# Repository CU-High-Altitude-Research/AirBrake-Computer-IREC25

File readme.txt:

https://github.com/CDFER/JLCPCB-Kicad-Library
To add library: git submodule add https://github.com/CDFER/JLCPCB-Kicad-Library.git
To update: git submodule update --remote

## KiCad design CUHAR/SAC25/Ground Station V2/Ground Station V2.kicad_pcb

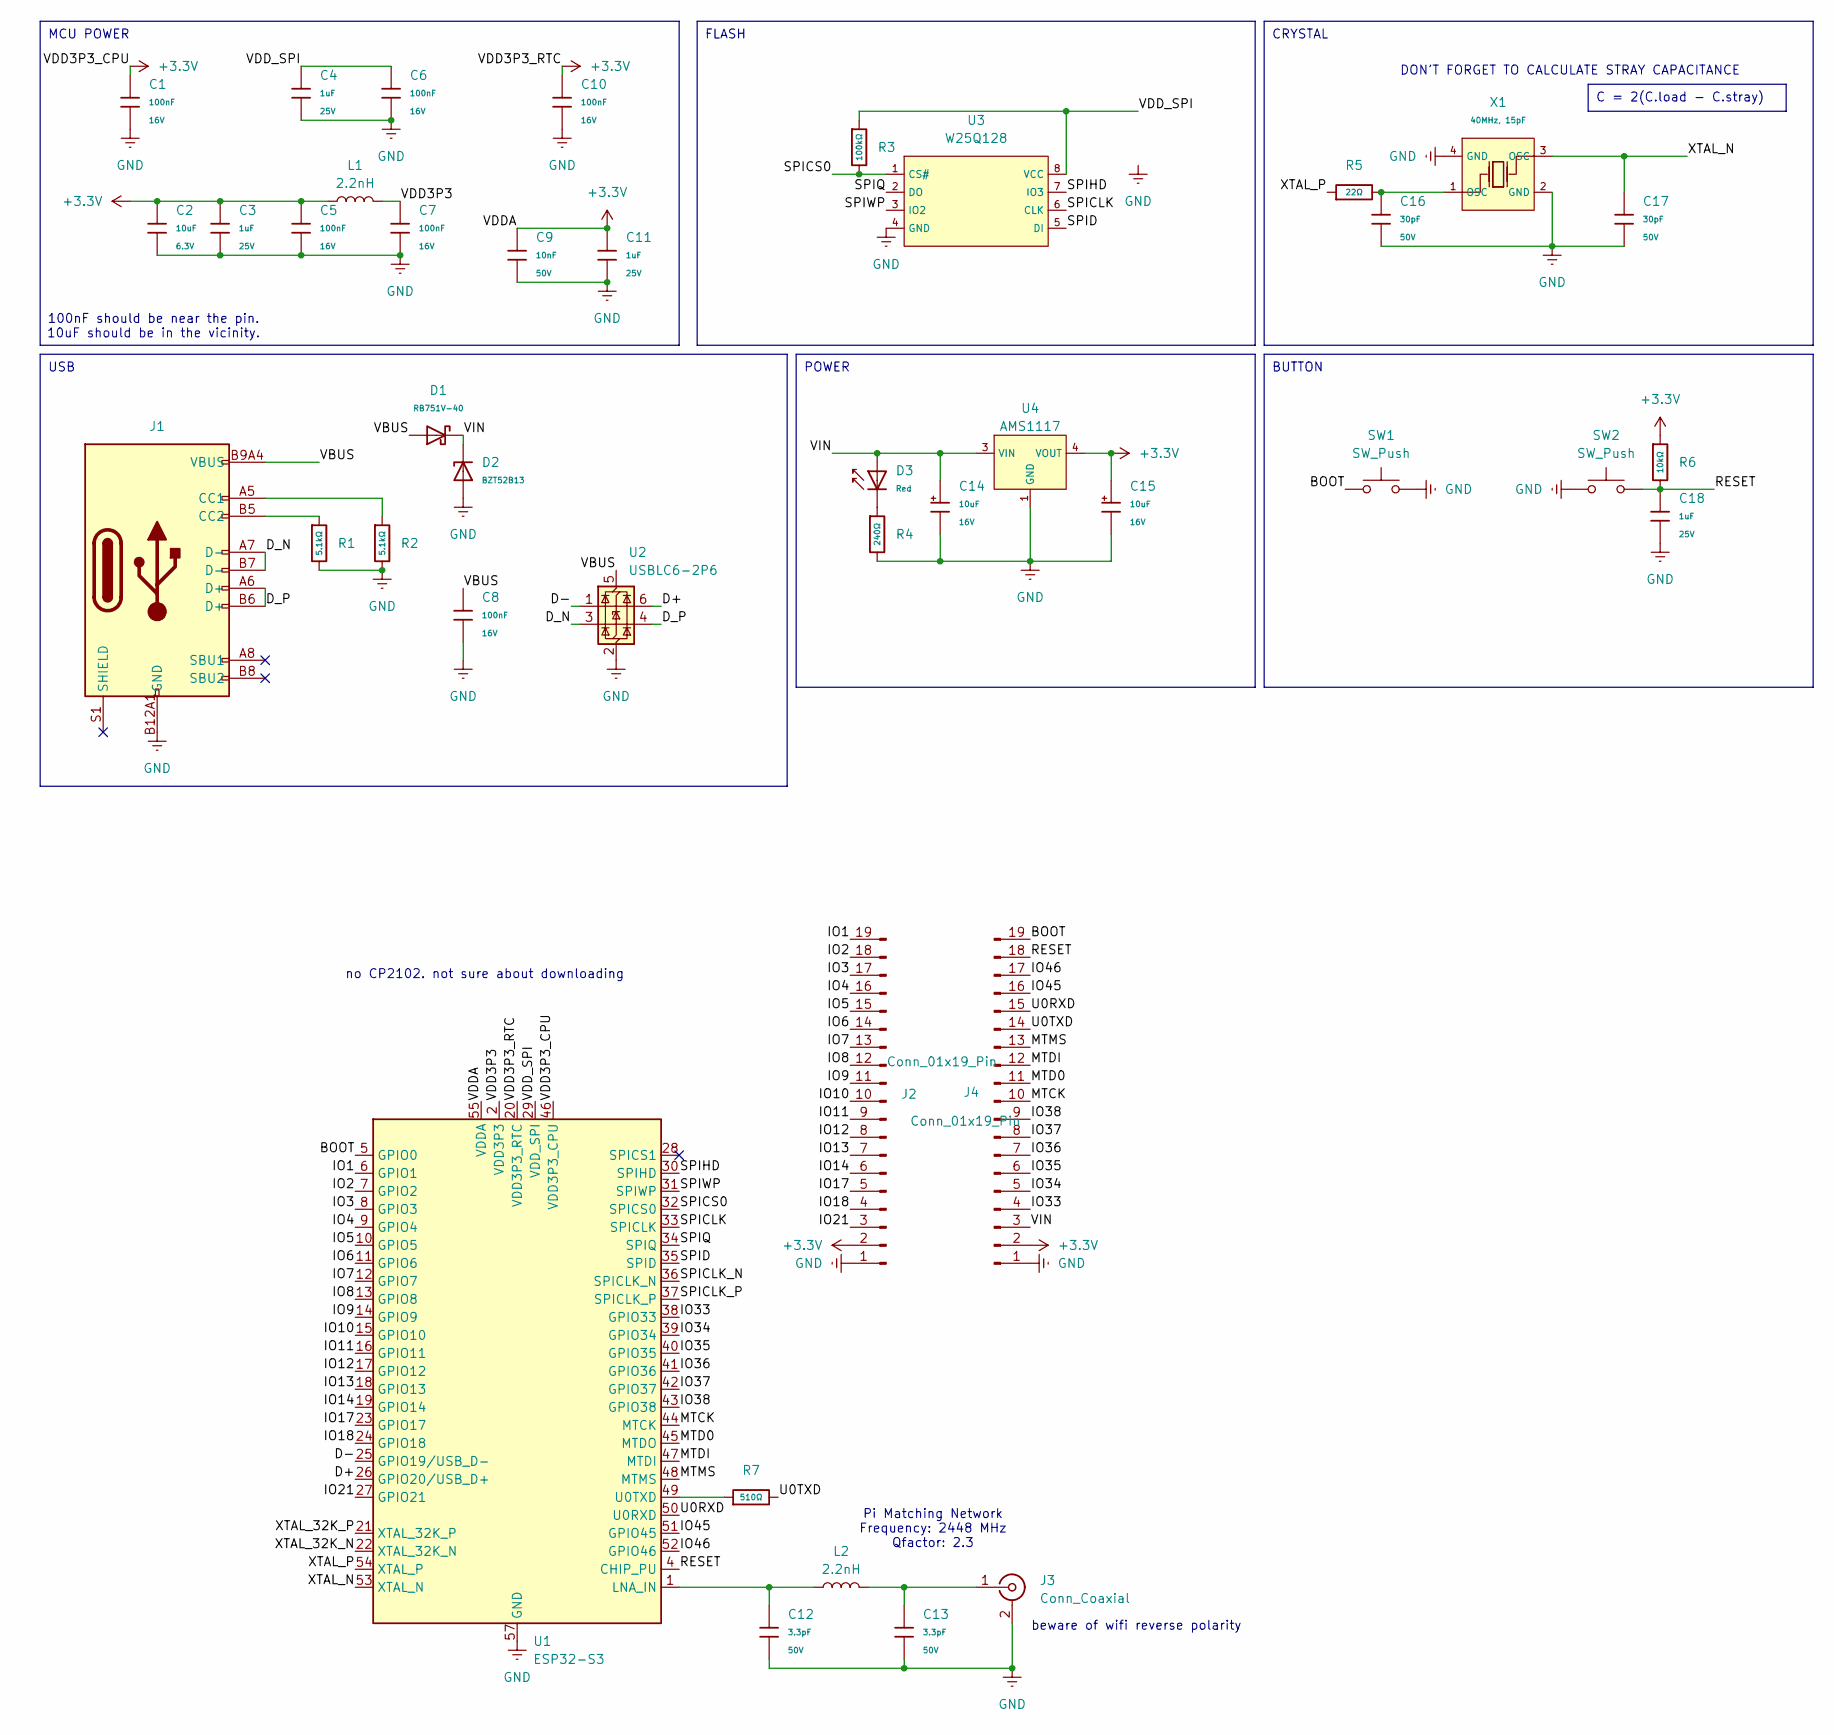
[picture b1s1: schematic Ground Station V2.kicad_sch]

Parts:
C1, C5, C6, C7, C8, C10: 100nF; C_0402; Voltage Rated 16V; Tolerance ±10%; Part CL05B104KO5NNNC; LCSC C1525
C2: 10uF; C_0402; Voltage Rated 6.3V; Tolerance ±20%; Part CL05A106MQ5NUNC; LCSC C15525
C3, C4, C11, C18: 1uF; C_0402; Voltage Rated 25V; Tolerance ±10%; Part CL05A105KA5NQNC; LCSC C52923
C9: 10nF; C_0402; Voltage Rated 50V; Tolerance ±10%; Part CL05B103KB5NNNC; LCSC C15195
C12, C13: 3.3pF; C_0402; Voltage Rated 50V; Part 0402CG3R3C500NT; LCSC C1565
C14, C15: 10uF; C_CASE-A-3216-18(mm); Tolerance ±10%; Rated Voltage 16V; Part TAJA106K016RNJ; LCSC C7171
C16, C17: 30pF; C_0402; Voltage Rated 50V; Tolerance ±5%; Part 0402CG300J500NT; LCSC C1570
D1: RB751V-40; D_SOD-323; Forward Voltage (Vf@If) 370mV@1mA; Reverse Voltage (Vr) 40V; Part RB751V-40; LCSC C7502691
D2: BZT52B13; D_SOD-123; Part BZT52B13; LCSC C22399883
D3: Red; D_0603; Part KT-0603R; LCSC C2286
J1: Connector, USB-TYPE-C-16P; TYPE-C-SMD_HX-TYPE-C-16PIN; LCSC C2927039
J2, J4: Conn_01x19_Pin; PinSocket_1x19_P2.54mm_Vertical
J3: Conn_Coaxial; SMA_Amphenol_132289_EdgeMount
L1, L2: 2.2nH; L_0402; JLCPCB Part # C86061
R1, R2: 5.1kΩ; R_0402; Overload Voltage (Max) 50V; Tolerance ±1%; Part 0402WGF5101TCE; LCSC C25905
R3: 100kΩ; R_0402; Overload Voltage (Max) 50V; Tolerance ±1%; Part 0402WGF1003TCE; LCSC C25741
R4: 240Ω; R_0603; Overload Voltage (Max) 75V; Tolerance ±1%; Part 0603WAF2400T5E; LCSC C23350
R5: 22Ω; R_0402; Overload Voltage (Max) 50V; Tolerance ±1%; Part 0402WGF220JTCE; LCSC C25092
R6: 10kΩ; R_0402; Overload Voltage (Max) 50V; Tolerance ±1%; Part 0402WGF1002TCE; LCSC C25744
R7: 510Ω; R_0402; Overload Voltage (Max) 50V; Tolerance ±1%; Part 0402WGF5100TCE; LCSC C25123
SW1, SW2: SW_Push; SW_Push_SPST_NO_Alps_SKRK
U1: ESP32-S3; QFN-56-1EP_7x7mm_P0.4mm_EP4x4mm_ThermalVias; LCSC C2913192
U2: USBLC6-2P6; SOT-666
U3: W25Q128; SOIC-8_L5.3-W5.3-P1.27-LS8.0-BL; Part W25Q128JVSIQ; LCSC C97521
U4: AMS1117; SOT-223-3_L6.5-W3.4-P2.30-LS7.0-BR; Output Voltage 3.3V; Dropout Voltage 1.3V@(800mA); Part AMS1117-3.3; LCSC C6186
X1: 40MHz, 15pF; OSC-SMD_4P-L3.2-W2.5-BL_SIT8008BI; PartID X322540MPB4SI; LCSC C9010

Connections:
+3.3V: C1.1, C2.1, C3.1, C5.1, C9.1, C10.1, C11.1, C15.1, J2.2, J4.2, L1.1, R6.1, U1.20 (VDD3P3_RTC), U1.46 (VDD3P3_CPU), U1.55 (VDDA), U1.56 (VDDA), U4.2 (VOUT), U4.4 (VOUT)
/BOOT: J4.19, SW1.1, U1.5 (GPIO0)
/D+: U1.26 (GPIO20/USB_D+), U2.6 (I/O1)
/D-: U1.25 (GPIO19/USB_D-), U2.1 (I/O1)
/D_N: J1.A7 (D-), J1.B7 (D-), U2.3 (I/O2)
/D_P: J1.A6 (D+), J1.B6 (D+), U2.4 (I/O2)
/IO1: J2.19, U1.6 (GPIO1)
/IO2: J2.18, U1.7 (GPIO2)
/IO3: J2.17, U1.8 (GPIO3)
/IO4: J2.16, U1.9 (GPIO4)
/IO5: J2.15, U1.10 (GPIO5)
/IO6: J2.14, U1.11 (GPIO6)
/IO7: J2.13, U1.12 (GPIO7)
/IO8: J2.12, U1.13 (GPIO8)
/IO9: J2.11, U1.14 (GPIO9)
/IO10: J2.10, U1.15 (GPIO10)
/IO11: J2.9, U1.16 (GPIO11)
/IO12: J2.8, U1.17 (GPIO12)
/IO13: J2.7, U1.18 (GPIO13)
/IO14: J2.6, U1.19 (GPIO14)
/IO17: J2.5, U1.23 (GPIO17)
/IO18: J2.4, U1.24 (GPIO18)
/IO21: J2.3, U1.27 (GPIO21)
/IO33: J4.4, U1.38 (GPIO33)
/IO34: J4.5, U1.39 (GPIO34)
/IO35: J4.6, U1.40 (GPIO35)
/IO36: J4.7, U1.41 (GPIO36)
/IO37: J4.8, U1.42 (GPIO37)
/IO38: J4.9, U1.43 (GPIO38)
/IO45: J4.16, U1.51 (GPIO45)
/IO46: J4.17, U1.52 (GPIO46)
/MTCK: J4.10, U1.44 (MTCK)
/MTD0: J4.11, U1.45 (MTDO)
/MTDI: J4.12, U1.47 (MTDI)
/MTMS: J4.13, U1.48 (MTMS)
/RESET: C18.1, J4.18, R6.2, SW2.2, U1.4 (CHIP_PU)
/SPICLK: U1.33 (SPICLK), U3.6 (CLK)
/SPICLK_N: U1.36 (SPICLK_N)
/SPICLK_P: U1.37 (SPICLK_P)
/SPICS0: R3.2, U1.32 (SPICS0), U3.1 (CS#)
/SPID: U1.35 (SPID), U3.5 (DI)
/SPIHD: U1.30 (SPIHD), U3.7 (IO3)
/SPIQ: U1.34 (SPIQ), U3.2 (DO)
/SPIWP: U1.31 (SPIWP), U3.3 (IO2)
/U0RXD: J4.15, U1.50 (U0RXD)
/U0TXD: J4.14, R7.2
/VBUS: C8.1, D1.2, J1.A9B4 (VBUS), J1.B9A4 (VBUS), U2.5 (VBUS)
/VDD3P3: C7.1, L1.2, U1.2 (VDD3P3), U1.3 (VDD3P3)
/VDD_SPI: C4.1, C6.1, R3.1, U1.29 (VDD_SPI), U3.8 (VCC)
/VIN: C14.1, D1.1, D2.1, D3.2, J4.3, U4.3 (VIN)
/XTAL_32K_N: U1.22 (XTAL_32K_N)
/XTAL_32K_P: U1.21 (XTAL_32K_P)
/XTAL_N: C17.1, U1.53 (XTAL_N), X1.3 (OSC)
/XTAL_P: R5.1, U1.54 (XTAL_P)
GND: C1.2, C2.2, C3.2, C4.2, C5.2, C6.2, C7.2, C8.2, C9.2, C10.2, C11.2, C12.2, C13.2, C14.2, C15.2, C16.2, C17.2, C18.2, D2.2, J1.A12B1 (GND), J1.B12A1 (GND), J2.1, J3.2 (Ext), J4.1, R1.2, R2.2, R4.2, SW1.2, SW2.1, U1.57 (GND), U2.2 (GND), U3.4 (GND), U4.1 (GND), X1.2 (GND), X1.4 (GND)
unnamed: C16.1, R5.2, X1.1 (OSC)
unnamed: D3.1, R4.1
unnamed: J1.A5 (CC1), R2.1
unnamed: J1.B5 (CC2), R1.1
unnamed: C13.1, J3.1 (In), L2.2
unnamed: C12.1, L2.1, U1.1 (LNA_IN)
unnamed: R7.1, U1.49 (U0TXD)

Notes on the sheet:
C = 2(C.load - C.stray)
USB
POWER
MCU POWER
CRYSTAL
FLASH
BUTTON
DON'T FORGET TO CALCULATE STRAY CAPACITANCE
100nF should be near the pin. 10uF should be in the vicinity.
no CP2102. not sure about downloading
beware of wifi reverse polarity
Pi Matching Network Frequency: 2448 MHz Qfactor: 2.3

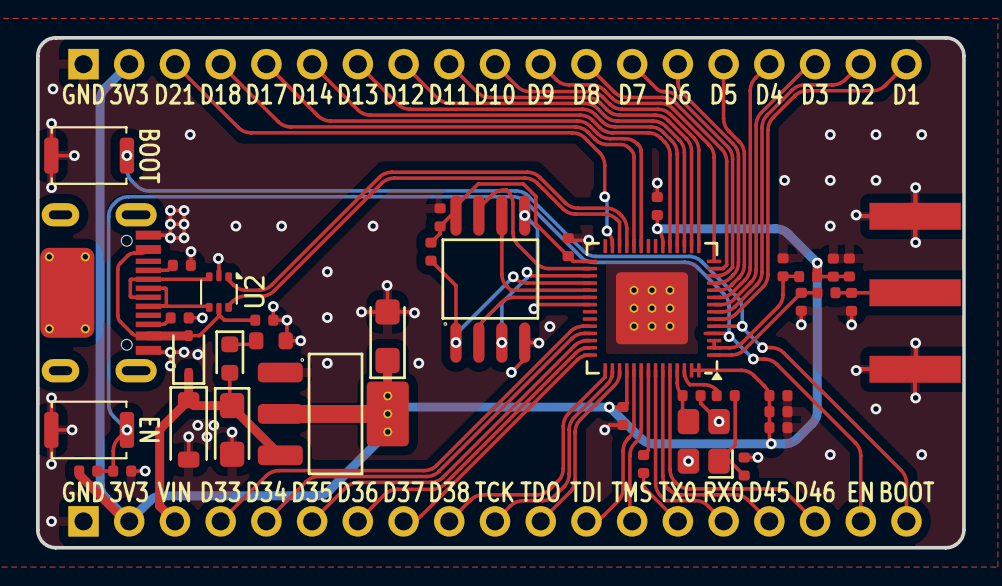
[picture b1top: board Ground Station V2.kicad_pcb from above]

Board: 2 copper layers, 51.5 x 28.3 mm, 41 parts (0 on the bottom side), 58 nets.

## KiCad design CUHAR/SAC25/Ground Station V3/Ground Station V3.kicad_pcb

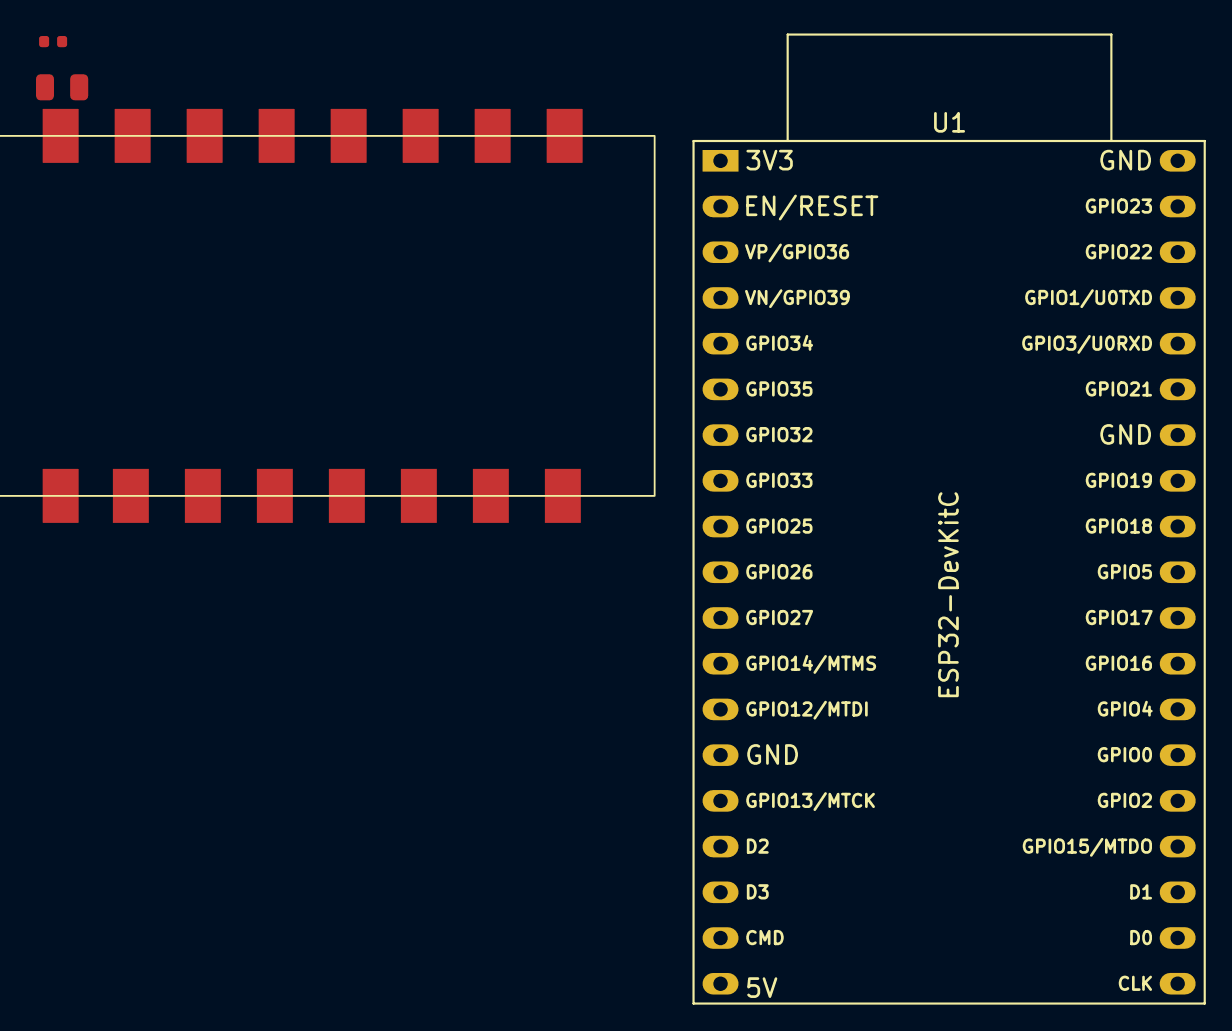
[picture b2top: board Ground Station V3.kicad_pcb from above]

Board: 2 copper layers, 4 parts (0 on the bottom side), 6 nets, no tracks yet.

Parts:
C1: 100nF; C_0402
C2: 47uF; C_0805
LoRa1262F1: LoRa1262F30
U1: ESP32-DevKitC

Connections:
/VSPI_CLK: LoRa1262F1.9 (SCK), U1.30 (GPIO18)
/VSPI_CS: LoRa1262F1.7 (NSS), U1.29 (GPIO5)
/VSPI_MISO: LoRa1262F1.10 (MISO), U1.31 (GPIO19)
/VSPI_MOSI: LoRa1262F1.11 (MOSI), U1.37 (GPIO23)
GND: C1.2, C2.2, LoRa1262F1.2 (GND), LoRa1262F1.8 (GND), U1.14 (GND), U1.32 (GND), U1.38 (GND)
unnamed: C1.1, C2.1, LoRa1262F1.1 (VCC)

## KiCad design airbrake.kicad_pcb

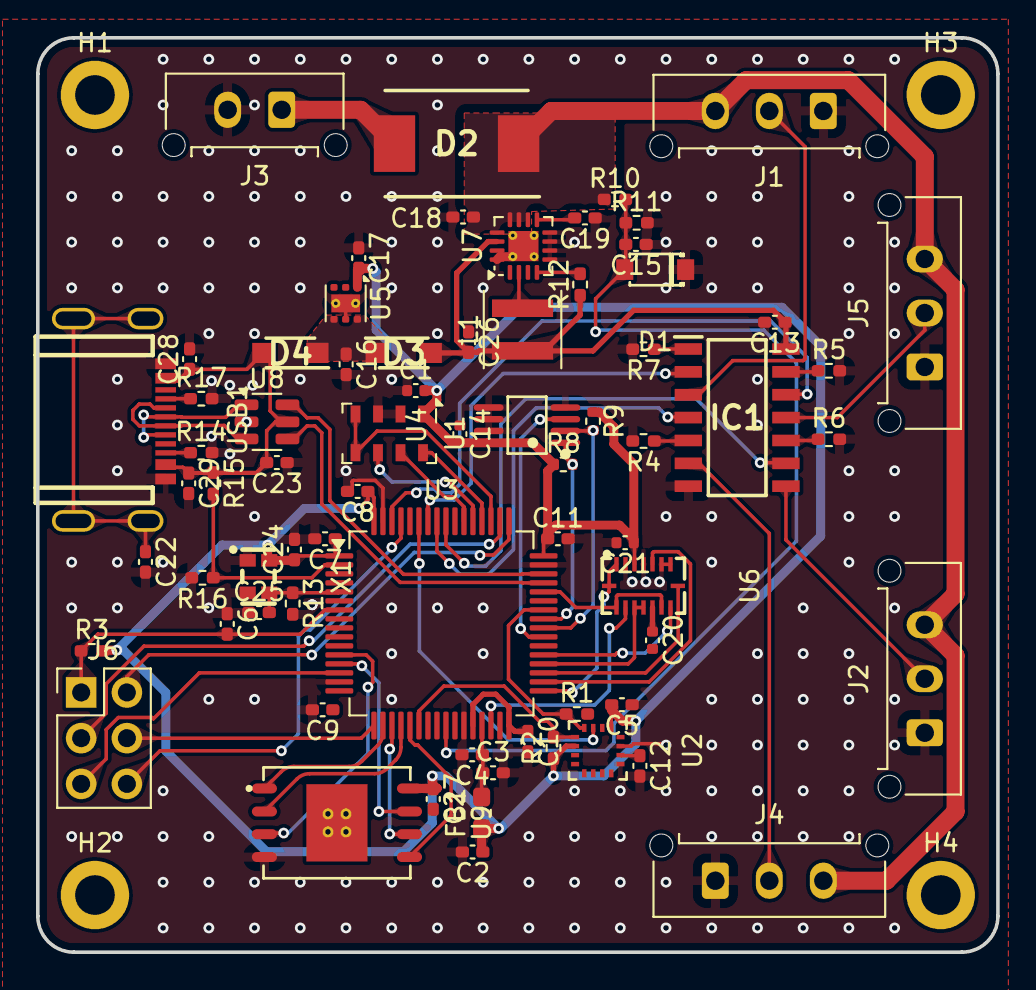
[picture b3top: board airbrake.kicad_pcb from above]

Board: 2 copper layers, 53.3 x 50.8 mm, 74 parts (0 on the bottom side), 60 nets.

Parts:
C1, C14, C20, C21: 100nF; C_0402_1005Metric
C2, C4, C5: 1uF; C_0402_1005Metric_Pad0.74x0.62mm_HandSolder
C3: 10nF; C_0402_1005Metric_Pad0.74x0.62mm_HandSolder
C6, C7, C8, C9, C10, C11, C15, C24, C27: 100nF; C_0402_1005Metric_Pad0.74x0.62mm_HandSolder
C12, C18, C23, C28, C29: 10uF; C_0402_1005Metric_Pad0.74x0.62mm_HandSolder
C13, C16: 100uF; C_0402_1005Metric_Pad0.74x0.62mm_HandSolder
C17: 2.2uF; C_0402_1005Metric_Pad0.74x0.62mm_HandSolder
C19: 3.3pF; C_0402_1005Metric_Pad0.74x0.62mm_HandSolder
C22: 1nF; C_0402_1005Metric_Pad0.74x0.62mm_HandSolder
C25: 10pF; C_0402_1005Metric_Pad0.74x0.62mm_HandSolder
C26: 22uF; C_0402_1005Metric_Pad0.74x0.62mm_HandSolder
D1: MMSZ4683T1G; SOD-123_L2.8-W1.8-LS3.7-RD
D2: SS34; DIOM7959X262N
D3, D4: NRVB120VLSFT1G; SODFL3616X98N
FB1: 100R; L_0603_1608Metric_Pad1.05x0.95mm_HandSolder
H1, H2, H3, H4: MountingHole; MountingHole_2.2mm_M2_DIN965_Pad
IC1: SN74HCT125DR; SOIC127P600X175-14N
J1, J2, J4, J5: Molex Microfit; Molex_Micro-Fit_3.0_43650-0315_1x03_P3.00mm_Vertical
J3: Molex Microfit; Molex_Micro-Fit_3.0_43650-0215_1x02_P3.00mm_Vertical
J6: Conn_02x03_Counter_Clockwise; PinHeader_2x03_P2.54mm_Vertical
L1: 2.2uH; L_Coilcraft_XxL4020
R1, R2: 4.7k; R_0402_1005Metric_Pad0.72x0.64mm_HandSolder
R3, R10, R15: 10k; R_0402_1005Metric_Pad0.72x0.64mm_HandSolder
R4, R5, R6, R7: 470R; R_0402_1005Metric_Pad0.72x0.64mm_HandSolder
R8, R9: 2.2k; R_0402_1005Metric
R11: 47k; R_0402_1005Metric_Pad0.72x0.64mm_HandSolder
R12, R13: 100k; R_0402_1005Metric_Pad0.72x0.64mm_HandSolder
R14, R17: 5.1k; R_0402_1005Metric_Pad0.72x0.64mm_HandSolder
R16: 22k; R_0402_1005Metric_Pad0.72x0.64mm_HandSolder
U1: MS5607-02BA; LGA-8_3x5mm_P1.25mm
U2: MMC5983MA; LGA-16_L3.0-W3.0-P0.50-BL_SQ
U3: STM32G431RBTx; LQFP-64_10x10mm_P0.5mm
U4: TMP275AIDGKR VSSOP8; VSSOP-8_L3.0-W3.0-P0.65-LS5.0-BL
U5: LP5912Q3.3DRVRQ1; WSON-6-1EP_2x2mm_P0.65mm_EP1x1.6mm_ThermalVias
U6: BMI088; LGA-16_L4.5-W3.0-P0.50-BL
U7: TPS62153; VQFN-16-1EP_3x3mm_P0.5mm_EP1.68x1.68mm_ThermalVias
U8: USBLC6-2SC6; SOT-23-6
U9: W25Q256JVEIQTR; WSON-8_L8.0-W6.10-P1.27-BL-EP
USB1: C169130; USB-C-SMD_TYPE-C3.1-02
X1: 1XXD32000MBA; OSC-SMD_4P-L2.0-W1.6-BL_1XXD

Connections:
+3.3V: C1.2, C2.1, C5.2, C7.1, C8.1, C9.1, C10.1, C11.1, C14.2, C17.2, C20.1, C21.1, C24.1, C27.1, FB1.1, R1.2, R2.1, R3.2, R8.1, R9.1, U1.1 (VDD), U2.2 (VDD), U2.13 (VDDIO), U3.1 (VBAT), U3.16 (VDD), U3.28 (VREF+), U3.32 (VDD), U3.48 (VDD), U3.64 (VDD), U4.8 (V+), U5.1 (OUT), U6.3 (VDD), U6.11 (VDDIO), U9.8 (VCC), X1.4 (VCC)
+3.3VA: C3.1, C4.1, FB1.2, U3.29 (VDDA)
+5V: C13.1, C26.2, D3.2 (A), IC1.14 (VCC), L1.1, R12.1, U7.14 (VOS)
/PWM_PD: IC1.1 (1~OE), IC1.5 (2A), IC1.10 (3~OE), IC1.13 (4~OE), R4.1, R5.1, R6.1, R7.1
BAT_LEVEL: C15.2, D1.2 (A), R10.2, R11.1, U3.25 (PB1)
BCD: R15.2, R16.1, U3.2 (PC13)
BMI088_ACCEL_CS: U3.30 (PB10), U6.14 (CSB1)
BMI088_ACCEL_INT: U3.33 (PB11), U6.1 (INT2), U6.16 (INT1)
BMI088_GYRO_CS: U3.34 (PB12), U6.5 (CSB2)
BMI088_GYRO_INT: U3.36 (PB14), U6.12 (INT3), U6.13 (INT4)
BMI088_MISO: U3.44 (PA10), U6.10 (SDO2), U6.15 (SDO1)
BMI088_MOSI: U3.37 (PB15), U6.9 (SDA/SDI)
BMI088_SCLK: U3.35 (PB13), U6.8 (SCL/SCK)
BOOT0: J6.6, U3.61 (PB8)
COMPANION_RX: J6.4, U3.17 (PA3)
COMPANION_TX: J6.5, U3.14 (PA2)
D+: U8.1 (I/O1), USB1.A6 (DP1), USB1.B6 (DP2)
D-: U8.3 (I/O2), USB1.A7 (DN1), USB1.B7 (DN2)
HSE_IN: C25.2, R13.1, U3.5 (PF0), X1.3 (Output)
MMC5983MA_INT: U2.15 (INT), U3.59 (PB6)
MMC5983MA_SCL: R2.2, U2.1 (SCL/SPI_SCK), U3.22 (PC4)
MMC5983MA_SDA: R1.1, U2.16 (SDA/SPI_SDI), U3.42 (PA8)
MS5607_MISO: U1.6 (SDO), U3.53 (PC11)
MS5607_MOSI: U1.7 (SDI/SDA), U3.54 (PC12)
MS5607_NSS: U1.4 (CSB), U1.5 (CSB), U3.51 (PA15)
MS5607_SCLK: U1.8 (SCLK), U3.52 (PC10)
unnamed: D2.2 (A), J3.1
unnamed: C16.1, D3.1 (K), D4.1 (K), U5.4 (EN), U5.6 (IN)
unnamed: L1.2, U7.1 (SW), U7.2 (SW), U7.3 (SW)
unnamed: C12.1, U2.10 (CAP)
unnamed: R12.2, U7.4 (PG)
unnamed: C19.2, U7.9 (SS/TR)
unnamed: R17.1, USB1.A5 (CC1)
unnamed: R14.1, USB1.B5 (CC2)
unnamed: C22.1, USB1.17 (EH)
PWM_A: IC1.2 (1A), U3.58 (PB5)
PWM_B: IC1.4 (2~OE), U3.57 (PB4)
PWM_C: IC1.9 (3A), U3.56 (PB3)
PWM_D: IC1.12 (4A), U3.62 (PB9)
SERVO_A: IC1.3 (1Y), J1.2
SERVO_B: IC1.6 (2Y), J4.2
SERVO_C: IC1.8 (3Y), J2.2
SERVO_D: IC1.11 (4Y), J5.2
SWCLK: J6.3, U3.50 (PA14)
SWDIO: J6.2, U3.49 (PA13)
TMP275_ALERT: U3.39 (PC7), U4.3 (ALERT)
TMP275_SCL: R9.2, U3.40 (PC8), U4.2 (SCL)
TMP275_SDA: R8.2, U3.41 (PC9), U4.1 (SDA)
USB_DN: U3.45 (PA11), U8.4 (I/O2)
USB_DP: U3.46 (PA12), U8.6 (I/O1)
VBAT+: C18.2, D2.1 (K), J1.3, J2.3, J4.3, J5.3, R10.1, U7.10 (VIN), U7.11 (VIN), U7.12 (VIN), U7.13 (EN)
VBAT-: C1.1, C2.2, C3.2, C4.2, C5.1, C6.1, C7.2, C8.2, C9.2, C10.2, C11.2, C12.2, C13.2, C14.1, C15.1, C16.2, C17.1, C18.1, C19.1, C20.2, C21.2, C22.2, C23.1, C24.2, C25.1, C26.1, C27.2, C28.2, C29.2, D1.1 (C), IC1.7 (GND), J1.1, J2.1, J3.2, J4.1, J5.1, R4.2, R5.2, R6.2, R7.2, R11.2, R13.2, R14.2, R16.2, R17.2, U1.2 (PS), U1.3 (GND), U2.9 (GND), U2.11 (GND), U3.15 (VSS), U3.27 (VSSA), U3.31 (VSS), U3.47 (VSS), U3.63 (VSS), U4.4 (GND), U4.5 (A2), U4.6 (A1), U4.7 (A0), U5.5 (GND), U5.7 (EP), U6.2 (NC), U6.4 (GNDA), U6.6 (GNDIO), U6.7 (PS), U7.5 (FB), U7.6 (GND), U7.7 (FSW), U7.8 (DEF), U7.15 (GND), U7.16 (GND), U7.17 (GND), U8.2 (GND), U9.4 (GND), USB1.A1 (GND), USB1.A12 (GND), USB1.B1 (GND), USB1.B12 (GND), X1.1 (GND), X1.2 (GND)
VBUS: C23.2, C28.1, C29.1, D4.2 (A), R15.1, U8.5 (VBUS), USB1.A4 (VBUS), USB1.A9 (VBUS), USB1.B4 (VBUS), USB1.B9 (VBUS)
W25Q_HOLD: U3.13 (PA1), U9.7 (HOLD#orRESET#(IO3))
W25Q_MISO: U3.20 (PA6), U9.2 (DO(IO1))
W25Q_MOSI: U3.21 (PA7), U9.5 (DI(IO0))
W25Q_NSS: U3.18 (PA4), U9.1 (~CS)
W25Q_SCK: U3.19 (PA5), U9.6 (CLK)
W25Q_WP: U3.12 (PA0), U9.3 (WP#(IO2))
nRST: C6.2, J6.1, R3.1, U3.7 (PG10)

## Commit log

2024-11-14 initialize rep
2024-12-10 hehehehar
2024-12-16 idk man
2024-12-16 meow
2024-12-16 delete
2024-12-16 um idk
2025-01-15 forgor to commit
2025-01-15 some minor update
2025-02-11 gitignore
2025-02-11 Added via stitching
2025-02-11 Completed trace routing
2025-02-11 minor fix
2025-02-11 Minor fix 2
2025-02-11 fillet trace
